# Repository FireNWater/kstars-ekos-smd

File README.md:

This is the Readme for my Raspberry Pi-5 Hat to control Astrophotography equipment.

This repository comes with absolutely NO Warranty, and is currently "in work".  There are several improvements I need to make to this design, the first of which is redesigning to use a larger format 5V buck converter.  The current buck converter is very small and difficult to solder using home shop air soldering techniques.

There is also a wiring bug in the 1-wire connections.  If you are going to use 1-wire, please connect directly to your Rpi or you will burn up your device and possibly the Rpi's power supply.

The UART connection works successfully.  Use ttyAMA0 and enable "UART0" on your Rpi.

I am planning on doing a complete rework of this design, hopefully before the end of 2025.  Planned improvements:

    1. Rework the Anderson Power Poles so they are used as stock instead of needing to be bent.
    2. Rework the APPs so they have a much more solid mount to the hat
    3. Extend the hat so it extends to the edge of the ethernet socket - more real estate
    4. I have found a larger 5V buck regulator that is much easier to solder using home hot air techniques
    5. Figure out why 1-wire circuit burns up the devices . . 
    6. There is a wiring bug that is fixed in the schematic, but is not fixed on the board traces.  This bug requires a bodge wire be installed on the 5V regulator to make it stable.  This is also very difficult to install.

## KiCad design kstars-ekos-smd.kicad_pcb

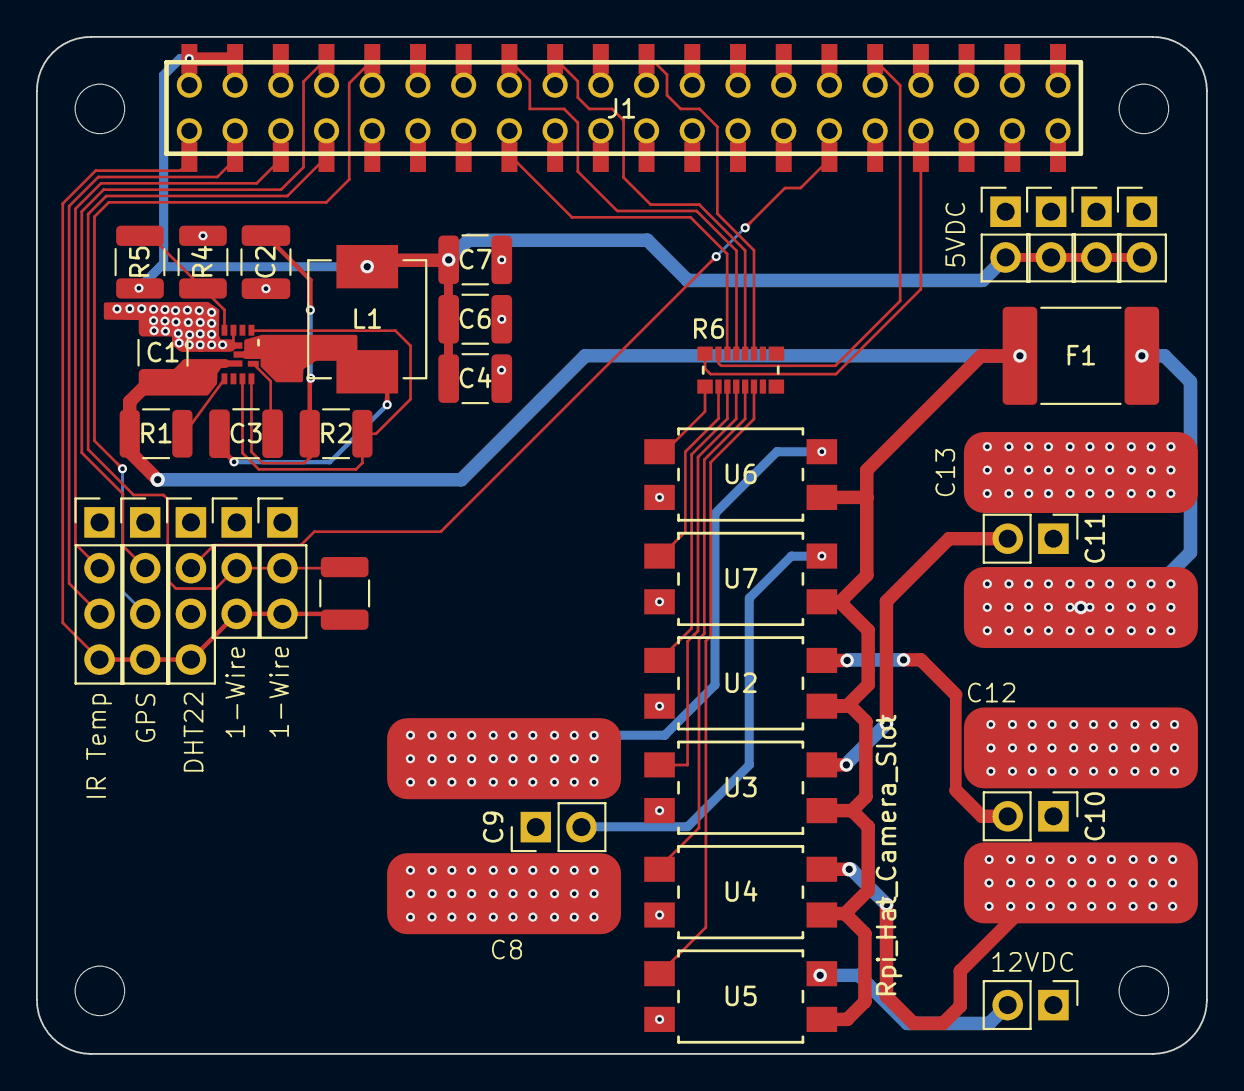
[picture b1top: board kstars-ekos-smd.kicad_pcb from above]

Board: 2 copper layers, 65.0 x 56.5 mm, 38 parts (0 on the bottom side), 35 nets.

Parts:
C1, C4, C6, C7: 22uF; C_1210_3225Metric
C2: 1uF; C_1210_3225Metric
C3: 100nF; C_1210_3225Metric
C8, C12, C13: Anderson Power Pole
C9, C10, C11: PinHeader_1x02_P2.54mm_Vertical
F1: Polyfuse - 6A; Fuse_2920_7451Metric
H1, H2, H3, H4, H5: MountingHole_Pad; PinHeader_1x02_P2.54mm_Vertical
J1: Raspberry_Pi_2_3; Raspberry_Pi_40_Pin_Header_With_Lands
J2, J4: Conn_01x03; PinHeader_1x03_P2.54mm_Vertical
J3, J5, J6: Conn_01x04; PinHeader_1x04_P2.54mm_Vertical
L1: 1.0uH; L_Vishay_IHLP-2525
R1, R2: 100K; R_1210_3225Metric
R3: 47k; R_1210_3225Metric
R4: 30.1K; R_1210_3225Metric
R5: 221K; R_1210_3225Metric
R6: 560 Ohm; RES_EXB2HV
U1: AP62600SJ-7; V-QFN2030-12_A_DIO
U2, U3, U4, U5: TLP3553ATP1_F; SOIC_3553ATP1_F_TOS
U6, U7: TLP241ATP1_F; SOIC_3553ATP1_F_TOS

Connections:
+3V3: J1.1 (3V3), J2.3, J3.4, J4.3, J5.4, J6.4, R3.2
+5V: C4.2, C6.2, C7.2, H1.1, H2.1, H3.1, H4.1, J1.2 (5V), J1.4 (5V), L1.2, R5.1
+12V: C1.2, F1.1, R1.1, U1.2 (VIN), U2.3, U3.3, U4.3, U5.3, U6.3, U7.3
DC1: R6.11, U2.1
DC2: R6.12, U3.1
DC3: R6.13, U4.1
DCX: R6.14, U5.1
DC_1: J1.15 (GPIO22), R6.6
DC_2: J1.16 (GPIO23), R6.5
DC_3: J1.18 (GPIO24), R6.4
DC_X: J1.22 (GPIO25), R6.3
DH1: R6.9, U6.1
DH2: R6.10, U7.1
Dew Heater 1: J1.33 (PWM1/GPIO13), R6.8
Dew Heater 2: J1.32 (PWM0/GPIO12), R6.7
GND: C1.1, C2.1, C4.1, C6.1, C7.1, C8.2 (Ground), C9.2 (Ground), C10.2 (Ground), C11.2 (Ground), C12.2 (Ground), C13.2 (Ground), H1.2, H2.2, H3.2, H4.2, H5.2, J1.6 (GND), J1.9 (GND), J1.14 (GND), J1.20 (GND), J1.25 (GND), J1.30 (GND), J1.34 (GND), J1.39 (GND), J2.1, J3.1, J4.1, J5.1, J6.1, R4.2, U1.1 (PGND), U1.11 (GND), U2.2, U3.2, U4.2, U5.2, U6.2, U7.2
unnamed: C8.1 (Positive), U6.4
unnamed: C9.1 (Positive), U7.4
unnamed: C10.1 (Positive), U2.4
unnamed: C11.1 (Positive), U3.4
unnamed: C12.1 (Positive), U4.4
unnamed: C13.1 (Positive), F1.2
unnamed: H5.1, U5.4
unnamed: J1.7 (GCLK0/GPIO4), J2.2, J4.2, R3.1
unnamed: J1.29 (GCLK1/GPIO5), J5.2
unnamed: C3.2, U1.7 (BST)
unnamed: R1.2, U1.3 (EN)
unnamed: R4.1, R5.2, U1.12 (FB)
unnamed: R2.1, U1.5 (FSEL), U1.9 (VCC)
unnamed: C2.2, R2.2, U1.6 (PG)
unnamed: C3.1, L1.1, U1.8 (SW)
RXD: J1.10 (GPIO15/RXD), J3.3
SCL i2c: J1.5 (SCL/GPIO3), J6.2
SDA i2c: J1.3 (SDA/GPIO2), J6.3
TXD: J1.8 (GPIO14/TXD), J3.2

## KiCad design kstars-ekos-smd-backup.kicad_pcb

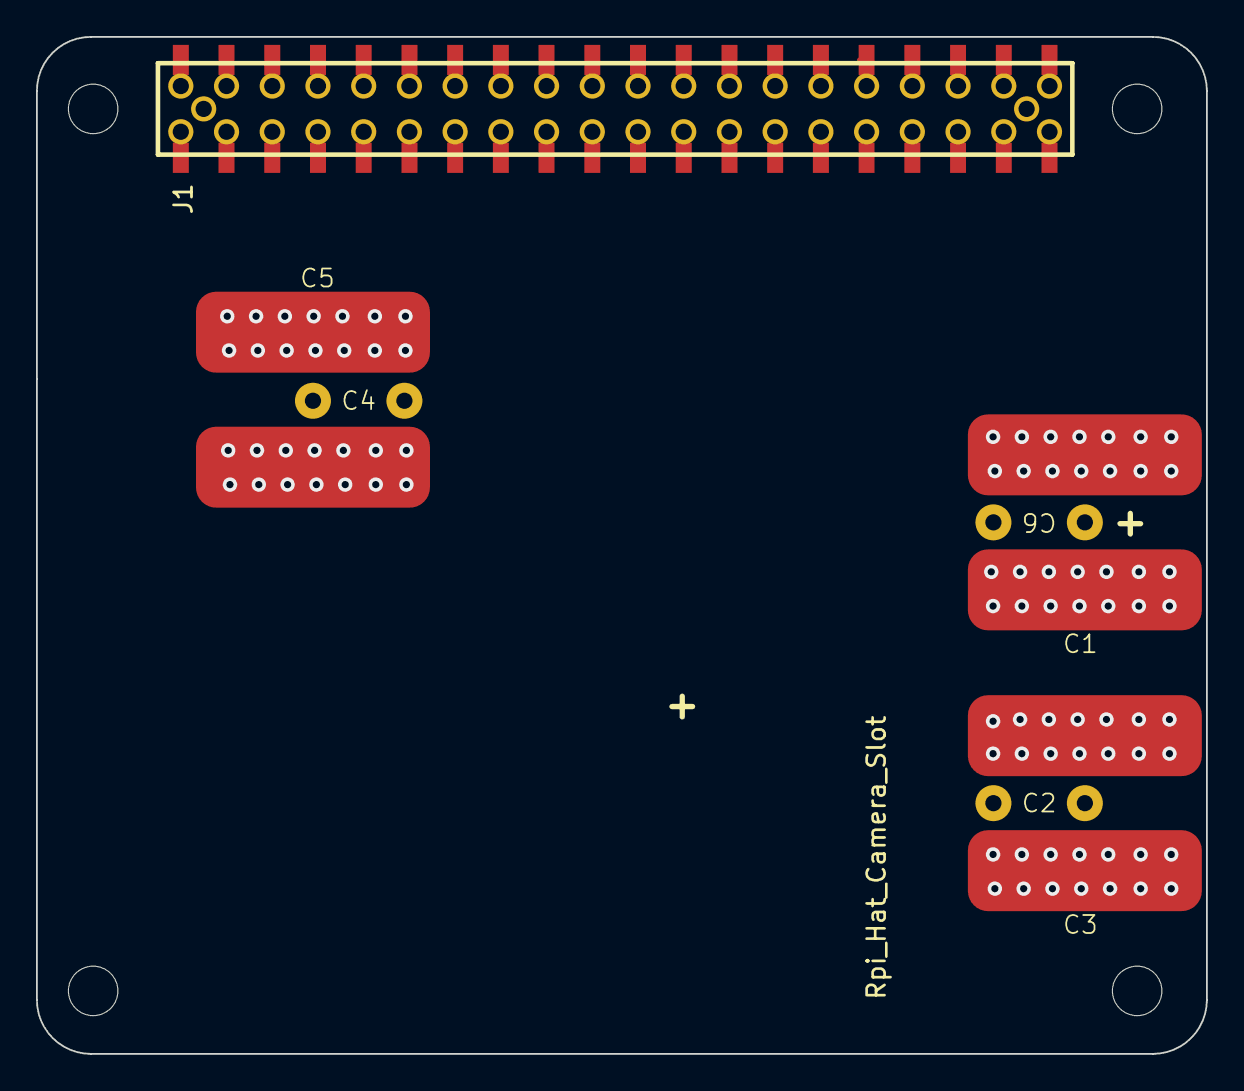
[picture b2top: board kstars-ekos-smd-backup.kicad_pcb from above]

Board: 2 copper layers, 65.0 x 56.5 mm, 7 parts (0 on the bottom side), 2 nets.

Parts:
C1, C3, C5: Anderson Power Pole
C2, C4, C6: APP Through-Hole
J1: Raspberry_Pi_2_3; Samtec_HLE-120-02-XXX-DV-BE-XX-XX

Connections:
+12V: C1.1 (Positive), C2.1 (Positive), C3.1 (Positive), C4.1 (Positive), C5.1 (Positive), C6.1 (Positive)
GND: C1.2 (Ground), C2.2 (Ground), C3.2 (Ground), C6.2 (Ground), J1.39 (GND)

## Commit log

2025-04-26 Initial Commit to GitHub
2025-04-26 New README
